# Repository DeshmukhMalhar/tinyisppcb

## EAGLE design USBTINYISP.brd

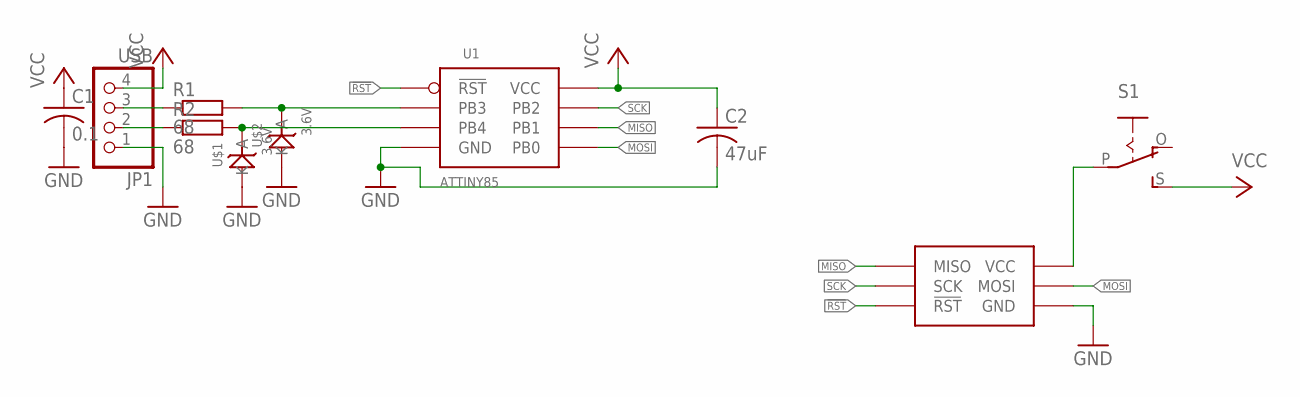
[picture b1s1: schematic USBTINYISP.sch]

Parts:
C1: 0.1; C025-025X050
C2: 47uF; C025-025X050
ICSP1: AVRISCP; AVRICSP
JP1: USB; 1X04
R1, R2: 68; 0207/7
S1: EG1218S; EG1218
U1: ATTINY85; DIP8
U$1, U$2: 3.6V; Z3V6

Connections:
!RST: ICSP1.P$5 (!RST), U1.P$1 (!RST)
GND: C1.2, C2.2, ICSP1.P$6 (GND), JP1.1, U1.P$4 (GND), U$1.P$2 (A), U$2.P$2 (A)
MISO: ICSP1.P$1 (MISO), U1.P$6 (PB1)
MOSI: ICSP1.P$4 (MOSI), U1.P$5 (PB0)
unnamed: JP1.3, R1.1
unnamed: JP1.2, R2.1
unnamed: R2.2, U1.P$3 (PB4), U$1.P$1 (K)
unnamed: R1.2, U1.P$2 (PB3), U$2.P$1 (K)
unnamed: ICSP1.P$2 (VCC), S1.P
SCK: ICSP1.P$3 (SCK), U1.P$7 (PB2)
VCC: C1.1, C2.1, JP1.4, S1.S, U1.P$8 (VCC)

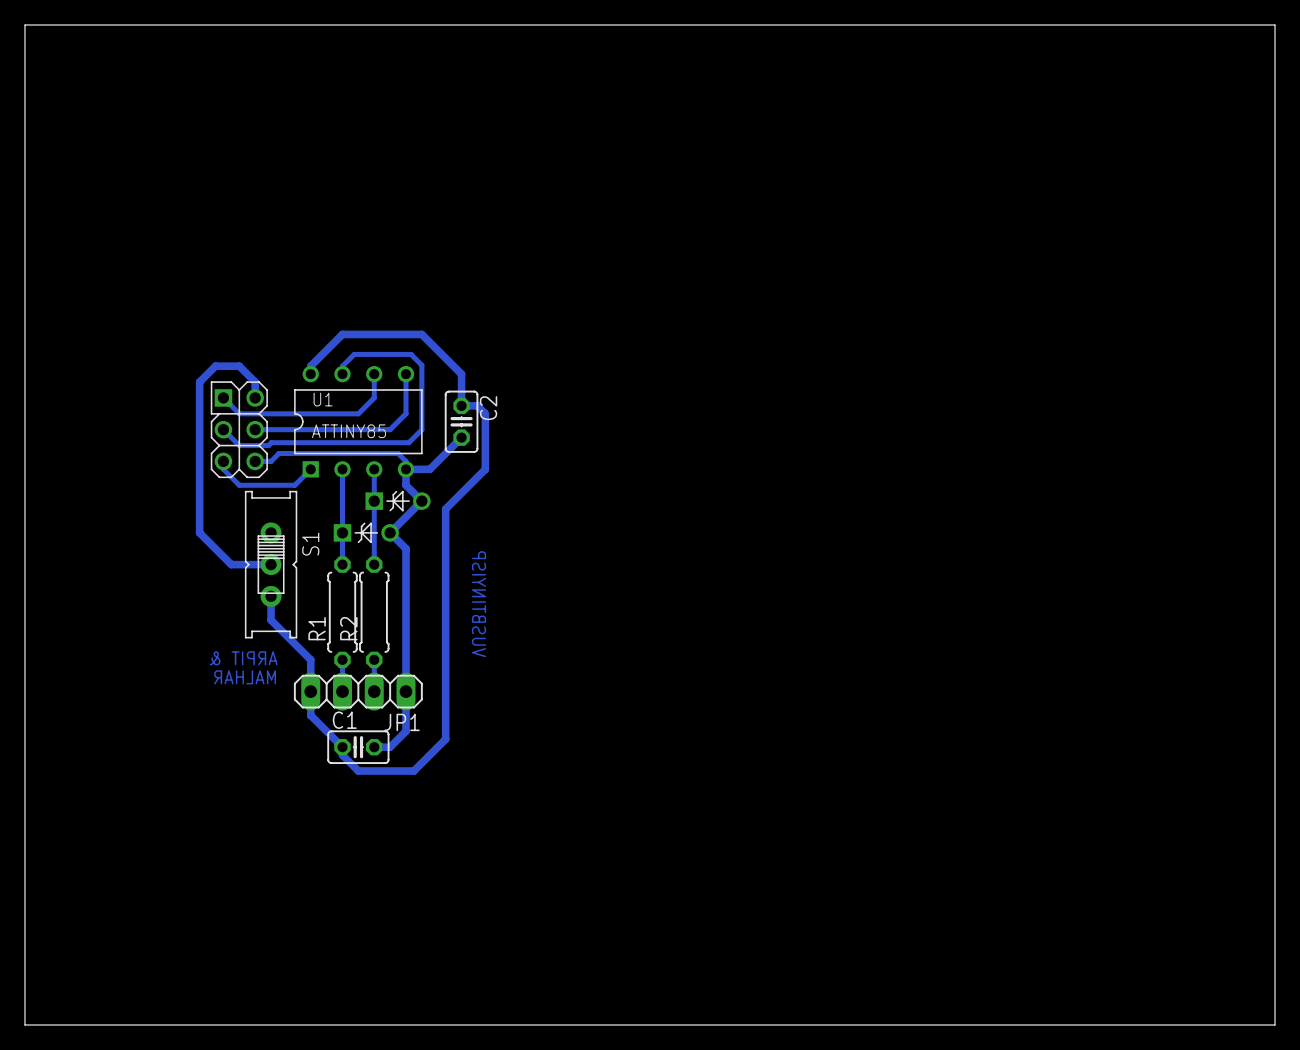
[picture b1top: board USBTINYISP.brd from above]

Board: 2 copper layers, 100.0 x 80.0 mm, 10 parts (0 on the bottom side), 11 nets.

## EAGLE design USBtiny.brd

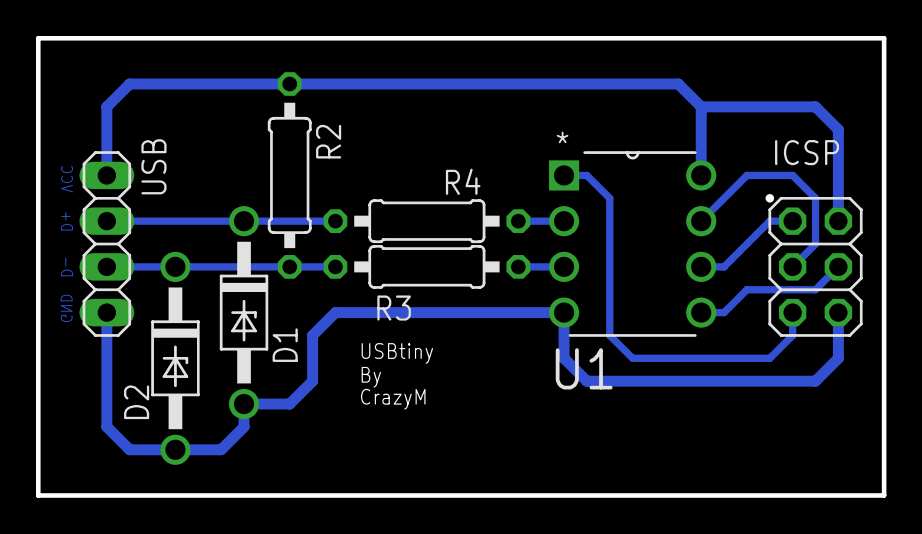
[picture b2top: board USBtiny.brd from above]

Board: 2 copper layers, 47.0 x 25.4 mm, 8 parts (0 on the bottom side), 10 nets.

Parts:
D1, D2: DO41Z10
ICSP: C2; 2X03
R2: 1K7; 0207/10
R3, R4: 68R; 0207/10
U1: ATTINY85-20PU; DIP254P762X533-8
USB: C1; 1X04

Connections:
+5V: ICSP.2, R2.1, U1.8, USB.4
GND: D1.A, D2.A, ICSP.6, U1.4, USB.1
unnamed: R4.2, U1.2
unnamed: R3.2, U1.3
unnamed: D2.C, R2.2, R3.1, USB.2
unnamed: D1.C, R4.1, USB.3
unnamed: ICSP.5, U1.1
unnamed: ICSP.1, U1.6
unnamed: ICSP.3, U1.7
unnamed: ICSP.4, U1.5

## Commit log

2017-09-10 ignore this
    ignore this
2017-09-10 corrected GND polygon
2017-09-10 Added IDs
